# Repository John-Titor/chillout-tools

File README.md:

# chillout-tools
reomote protocol tools etc. for the Chillout Systems family of personal cooling systems

# decoder.py
simple serial protocol decoder for the remote <-> compressor protocol

# AnalogInterface
Firmware, schematic and PCB for an adapter that allows the use of a Chillout Quantum V3 (and probably others with minor changes) with a CoolShirt controller.

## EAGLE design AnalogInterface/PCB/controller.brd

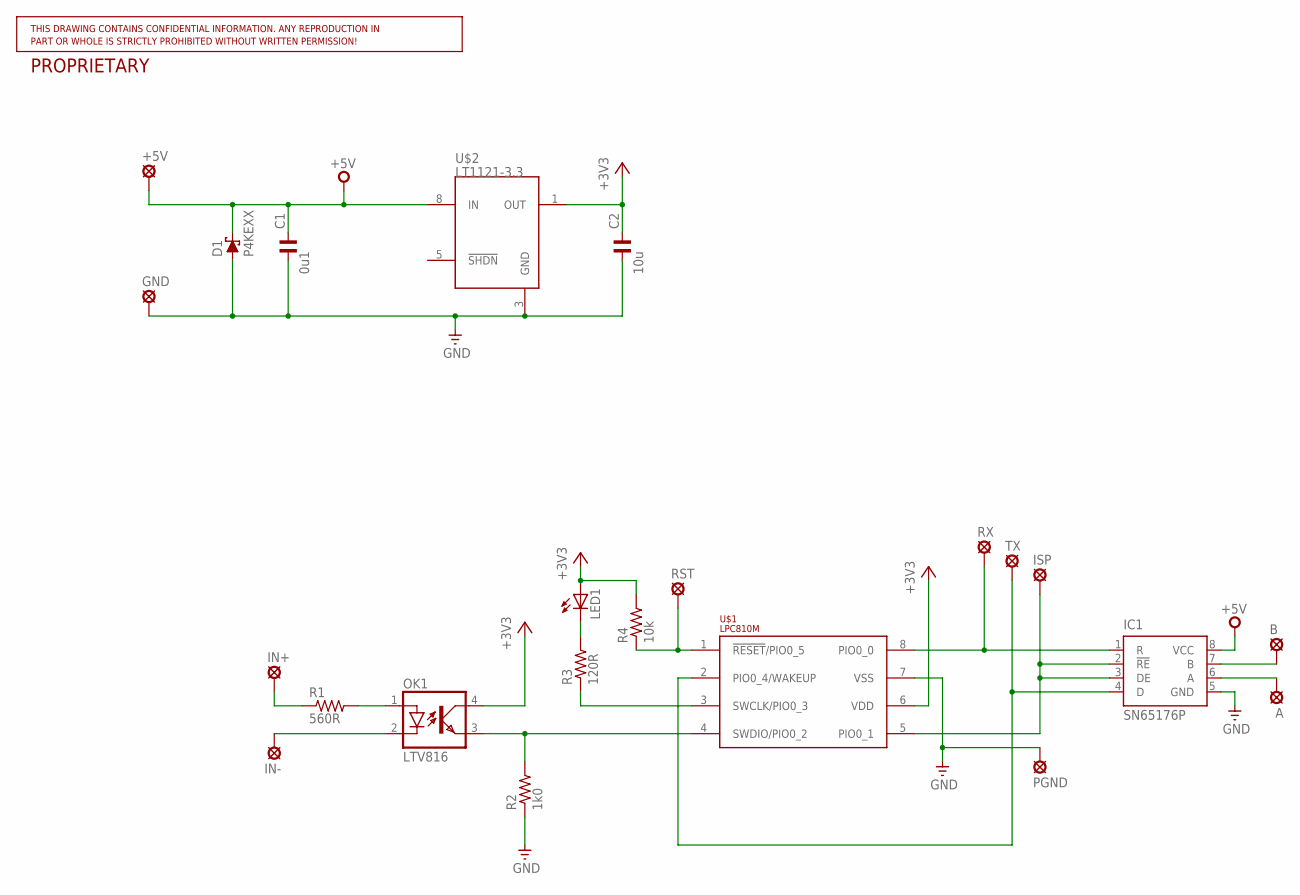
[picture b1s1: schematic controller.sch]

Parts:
+5V: SE14
A: SE14
B: SE14
C1: 0u1; C050-024X044
C2: 10u; C050-024X044
D1: P4KEXX; DO41-10
GND: SE14
IC1: SN65176P; DIL08
IN+: SE14
IN-: SE14
ISP: SE14
LED1: LED-3MM-NO_SILK; LED3MM-NS
OK1: LTV816; DIL04
PGND: SE14
R1: 560R; 0207/10B
R2: 1k0; 0207/10B
R3: 120R; 0207/10B
R4: 10k; 0207/10B
RST: SE14
RX: SE14
TX: SE14
U$1: LPC810M; DIL08
U$2: LT1121-3.3; DIL08

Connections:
+3V3: C2.1, LED1.A, OK1.4 (COL), R4.2, U$1.6 (VDD), U$2.1 (OUT)
+5V: +5V.MP, C1.1, D1.C, IC1.8 (VCC), U$2.8 (IN)
GND: C1.2, C2.2, D1.A, GND.MP, IC1.5 (GND), PGND.MP, R2.1, U$1.7 (VSS), U$2.3 (GND)
unnamed: IC1.1 (R), RX.MP, U$1.8 (PIO0_0)
unnamed: IN+.MP, R1.1
unnamed: OK1.1 (A), R1.2
unnamed: IN-.MP, OK1.2 (C)
unnamed: OK1.3 (EMIT), R2.2, U$1.4 (SWDIO/PIO0_2)
unnamed: IC1.4 (D), TX.MP, U$1.2 (PIO0_4/WAKEUP)
unnamed: IC1.2 (!RE), IC1.3 (DE), ISP.MP, U$1.5 (PIO0_1)
unnamed: LED1.K (C), R3.2
unnamed: B.MP, IC1.7 (B)
unnamed: A.MP, IC1.6 (A)
unnamed: R3.1, U$1.3 (SWCLK/PIO0_3)
unnamed: R4.1, RST.MP, U$1.1 (!RESET!/PIO0_5)

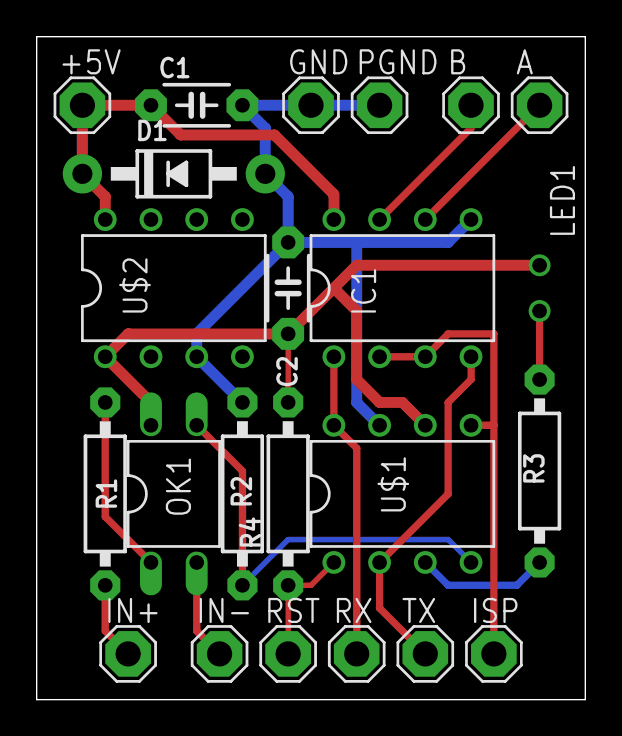
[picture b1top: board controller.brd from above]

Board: 2 copper layers, 30.5 x 36.8 mm, 23 parts (0 on the bottom side), 15 nets.

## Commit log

2022-04-08 initial remote protocol decoder for Quantum v3 only
2022-04-08 bring packet format comments into line with code
2022-04-08 add pinout details
2022-04-18 Add CoolShirt analog controller interface
2022-04-18 teach decoder about 'off in max' state
2022-04-18 add schematic PDF, remove confidentiality notice
2022-04-18 revise LICENSE
2022-04-18 Create LICENSE
2022-08-16 Tools for working with the Chillout Quantum personal cooler remote protocol.
